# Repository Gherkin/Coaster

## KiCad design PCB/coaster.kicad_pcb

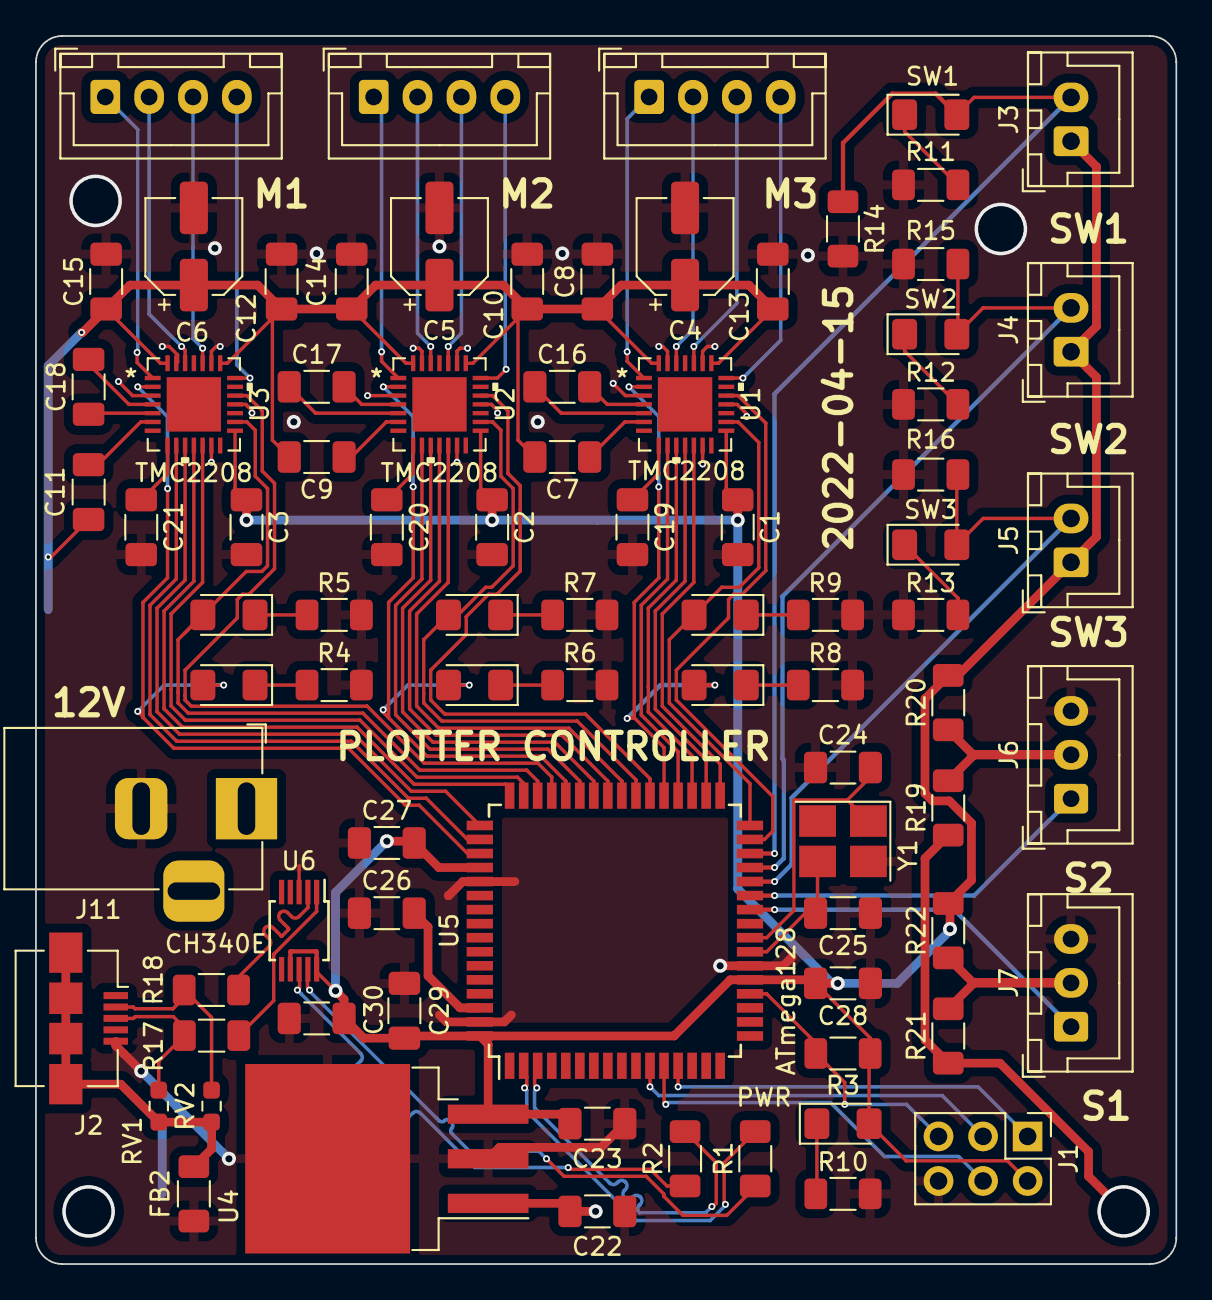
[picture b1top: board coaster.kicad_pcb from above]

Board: 2 copper layers, 65.0 x 70.0 mm, 83 parts (0 on the bottom side), 81 nets.

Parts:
C1, C2, C3, C7, C8, C9, C10, C11, C12, C13, C14, C15, C23, C26, C27, C28, C29, C30: 100n; C_1206_3216Metric_Pad1.33x1.80mm_HandSolder
C4, C5, C6: 100u; CP_Elec_5x5.4
C16, C17, C18: 22n; C_1206_3216Metric_Pad1.33x1.80mm_HandSolder
C19, C20, C21: 2.2u; C_1206_3216Metric_Pad1.33x1.80mm_HandSolder
C22: 0.33u; C_1206_3216Metric_Pad1.33x1.80mm_HandSolder
C24, C25: 20p; C_1206_3216Metric_Pad1.33x1.80mm_HandSolder
D1: M1EN; LED_1206_3216Metric_Pad1.42x1.75mm_HandSolder
D2: M1STEP; LED_1206_3216Metric_Pad1.42x1.75mm_HandSolder
D3: M2EN; LED_1206_3216Metric_Pad1.42x1.75mm_HandSolder
D4: M2STEP; LED_1206_3216Metric_Pad1.42x1.75mm_HandSolder
D5: M3EN; LED_1206_3216Metric_Pad1.42x1.75mm_HandSolder
D6: M3STEP; LED_1206_3216Metric_Pad1.42x1.75mm_HandSolder
D7: PWR; LED_1206_3216Metric_Pad1.42x1.75mm_HandSolder
D8: SW1; LED_1206_3216Metric_Pad1.42x1.75mm_HandSolder
D9: SW2; LED_1206_3216Metric_Pad1.42x1.75mm_HandSolder
D10: SW3; LED_1206_3216Metric_Pad1.42x1.75mm_HandSolder
FB2: FerriteBead; R_1206_3216Metric_Pad1.30x1.75mm_HandSolder
J1: AVR-ISP-6; PinHeader_2x03_P2.54mm_Vertical
J2: USB_B_Micro; USB_Micro-B_Amphenol_10104110_Horizontal
J3, J4, J5: Conn_01x02; JST_XH_B2B-XH-A_1x02_P2.50mm_Vertical
J6, J7: Conn_01x03; JST_XH_B3B-XH-A_1x03_P2.50mm_Vertical
J8, J9, J10: Conn_01x04; JST_XH_B4B-XH-A_1x04_P2.50mm_Vertical
J11: Barrel_Jack; BarrelJack_Horizontal
R1, R2: 1k; R_1206_3216Metric_Pad1.30x1.75mm_HandSolder
R3, R14, R15, R16: 10k; R_1206_3216Metric_Pad1.30x1.75mm_HandSolder
R4, R6, R8, R10: 100; R_1206_3216Metric_Pad1.30x1.75mm_HandSolder
R5, R7, R9, R11, R12, R13: 120; R_1206_3216Metric_Pad1.30x1.75mm_HandSolder
R17, R18: 22; R_1206_3216Metric_Pad1.30x1.75mm_HandSolder
R19, R20, R21, R22: 0; R_1206_3216Metric_Pad1.30x1.75mm_HandSolder
RV1, RV2: CG0603MLC-05E; R_0603_1608Metric_Pad0.98x0.95mm_HandSolder
U1, U2, U3: TMC2208; TMC2208-LA
U4: uA7805; TO-263-3_TabPin2
U5: ATmega128; TQFP-64_14x14mm_P0.8mm
U6: CH340E; MSOP-10_3x3mm_P0.5mm
Y1: 16MHz 12pF 60 Ohm +/- 10 ppm; Crystal_SMD_3225-4Pin_3.2x2.5mm_HandSoldering

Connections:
/5V: C1.1, C2.1, C3.1, C23.1, C27.2, C28.2, C29.1, C30.1, D7.2 (A), J1.2 (VCC), J3.1, J4.1, J5.1, R3.1, R20.2, R22.2, U1.15 (VCC_IO), U2.15 (VCC_IO), U3.15 (VCC_IO), U4.3 (OUT), U5.21 (VCC), U5.52 (VCC), U5.64 (AVCC), U6.7 (VCC), U6.10 (V3)
/9V: C4.1, C5.1, C6.1, C7.2, C8.1, C9.2, C10.1, C11.2, C12.1, C13.1, C14.1, C15.1, C22.1, J11.1, R19.1, R21.1, U1.22 (VS), U1.28 (VS), U2.22 (VS), U2.28 (VS), U3.22 (VS), U3.28 (VS), U4.1 (IN)
/AUART_N: R2.2, U5.3 (PE1)
/AUART_P: R1.2, U5.2 (PE0)
/M1AO1: J8.3, U3.24 (OA1)
/M1AO2: J8.4, U3.21 (OA2)
/M1BO1: J8.2, U3.26 (OB1)
/M1BO2: J8.1, U3.1 (OB2)
/M1CPI: C18.1, U3.5 (CPI)
/M1CPO: C18.2, U3.4 (CPO)
/M1DIAG: U3.11 (DIAG), U5.48 (PA3)
/M1DIR: U3.19 (DIR), U5.45 (PA6)
/M1EN: D1.2 (A), U3.2 (ENN), U5.51 (PA0)
/M1INDEX: U3.12 (INDEX), U5.47 (PA4)
/M1MS1: U3.9 (MS1), U5.50 (PA1)
/M1MS2: U3.10 (MS2), U5.49 (PA2)
/M1STEP: D2.2 (A), U3.16 (STEP), U5.46 (PA5)
/M2AO1: J9.3, U2.24 (OA1)
/M2AO2: J9.4, U2.21 (OA2)
/M2BO1: J9.2, U2.26 (OB1)
/M2BO2: J9.1, U2.1 (OB2)
/M2CPI: C17.1, U2.5 (CPI)
/M2CPO: C17.2, U2.4 (CPO)
/M2DIAG: U2.11 (DIAG), U5.41 (PC6)
/M2DIR: U2.19 (DIR), U5.38 (PC3)
/M2EN: D3.2 (A), U2.2 (ENN), U5.44 (PA7)
/M2INDEX: U2.12 (INDEX), U5.40 (PC5)
/M2MS1: U2.9 (MS1), U5.43 (PG2)
/M2MS2: U2.10 (MS2), U5.42 (PC7)
/M2STEP: D4.2 (A), U2.16 (STEP), U5.39 (PC4)
/M3AO1: J10.3, U1.24 (OA1)
/M3AO2: J10.4, U1.21 (OA2)
/M3BO1: J10.2, U1.26 (OB1)
/M3BO2: J10.1, U1.1 (OB2)
/M3CPI: C16.1, U1.5 (CPI)
/M3CPO: C16.2, U1.4 (CPO)
/M3DIAG: U1.11 (DIAG), U5.34 (PG1)
/M3DIR: U1.19 (DIR), U5.31 (PD6)
/M3EN: D5.2 (A), U1.2 (ENN), U5.37 (PC2)
/M3INDEX: U1.12 (INDEX), U5.33 (PG0)
/M3MS1: U1.9 (MS1), U5.36 (PC1)
/M3MS2: U1.10 (MS2), U5.35 (PC0)
/M3STEP: D6.2 (A), U1.16 (STEP), U5.32 (PD7)
/MISO: J1.1 (MISO), U5.13 (PB3)
/MOSI: J1.4 (MOSI), U5.12 (PB2)
/RESET: J1.5 (~RST), R3.2, U5.20 (~RESET)
/S1: J7.1, U5.26 (PD1)
/S2: J6.1, U5.27 (PD2)
/SCK: J1.3 (SCK), U5.11 (PB1)
/SW1: D8.2 (A), J3.2, R14.1, U5.30 (PD5)
/SW2: D9.2 (A), J4.2, R15.1, U5.29 (PD4)
/SW3: D10.2 (A), J5.2, R16.1, U5.28 (PD3)
/UART_N: R2.1, U6.8 (TXD)
/UART_P: R1.1, U6.9 (RXD)
/UD+: R17.2, U6.1 (UD+)
/UD-: R18.2, U6.2 (UD-)
/UUD+: J2.3 (D+), R17.1, RV1.1
/UUD-: J2.2 (D-), R18.1, RV2.1
/shield: FB2.1, J2.6 (Shield), RV1.2, RV2.2
GND: C1.2, C2.2, C3.2, C4.2, C5.2, C6.2, C8.2, C10.2, C12.2, C13.2, C14.2, C15.2, C19.2, C20.2, C21.2, C22.2, C23.2, C24.1, C25.1, C26.1, C27.1, C28.1, C29.2, C30.2, FB2.2, J1.6 (GND), J2.5 (GND), J6.3, J7.3, J11.2, R4.2, R5.2, R6.2, R7.2, R8.2, R9.2, R10.2, R11.1, R12.1, R13.1, R14.2, R15.2, R16.2, U1.3 (GND), U1.13 (CLK), U1.18 (GND), U1.23 (BRA), U1.27 (BRB), U2.3 (GND), U2.13 (CLK), U2.18 (GND), U2.23 (BRA), U2.27 (BRB), U3.3 (GND), U3.13 (CLK), U3.18 (GND), U3.23 (BRA), U3.27 (BRB), U4.2 (GND), U5.22 (GND), U5.53 (GND), U5.63 (GND), U6.3 (GND), Y1.2 (GND), Y1.4 (GND)
unnamed: C7.1, U1.6 (VCP)
unnamed: C9.1, U2.6 (VCP)
unnamed: C11.1, U3.6 (VCP)
unnamed: C19.1, U1.8 (5VOUT)
unnamed: C20.1, U2.8 (5VOUT)
unnamed: C21.1, U3.8 (5VOUT)
unnamed: C24.2, U5.24 (XTAL1), Y1.1 (IN/OUT)
unnamed: C25.2, U5.23 (XTAL2), Y1.3 (OUT/IN)
unnamed: C26.2, U5.62 (AREF)
unnamed: D1.1 (K), R4.1
unnamed: D2.1 (K), R5.1
unnamed: D3.1 (K), R6.1
unnamed: D4.1 (K), R7.1
unnamed: D5.1 (K), R8.1
unnamed: D6.1 (K), R9.1
unnamed: D7.1 (K), R10.1
unnamed: D8.1 (K), R11.2
unnamed: D9.1 (K), R12.2
unnamed: D10.1 (K), R13.2
unnamed: J6.2, R19.2, R20.1
unnamed: J7.2, R21.2, R22.1

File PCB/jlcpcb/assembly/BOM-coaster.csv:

Comment,Designator,Footprint,LCSC
22n,"C16,C17,C18",C_1206_3216Metric_Pad1.33x1.80mm_HandSolder,C113907
TMC2208,"U1,U2,U3",TMC2208-LA,C115944
FerriteBead,FB2,R_1206_3216Metric_Pad1.30x1.75mm_HandSolder,C139169
20p,"C24,C25",C_1206_3216Metric_Pad1.33x1.80mm_HandSolder,C162447
0,"R19,R20,R21,R22",R_1206_3216Metric_Pad1.30x1.75mm_HandSolder,C17888
100,"R10,R4,R6,R8",R_1206_3216Metric_Pad1.30x1.75mm_HandSolder,C17901
10k,"R14,R15,R16,R3",R_1206_3216Metric_Pad1.30x1.75mm_HandSolder,C17902
120,"R11,R12,R13,R5,R7,R9",R_1206_3216Metric_Pad1.30x1.75mm_HandSolder,C17909
ATmega128,U5,TQFP-64_14x14mm_P0.8mm,C183188
CG0603MLC-05E,"RV1,RV2",R_0603_1608Metric_Pad0.98x0.95mm_HandSolder,C20960
100n,"C1,C10,C11,C12,C13,C14,C15,C2,C23,C26,C27,C28,C29,C3,C30,C7,C8,C9",C_1206_3216Metric_Pad1.33x1.80mm_HandSolder,C24497
0.33u,C22,C_1206_3216Metric_Pad1.33x1.80mm_HandSolder,C307572
1k,"R1,R2",R_1206_3216Metric_Pad1.30x1.75mm_HandSolder,C4410
100u,"C4,C5,C6",CP_Elec_5x5.4,C487302
2.2u,"C19,C20,C21",C_1206_3216Metric_Pad1.33x1.80mm_HandSolder,C50254
22,"R17,R18",R_1206_3216Metric_Pad1.30x1.75mm_HandSolder,C5672
M1EN,"D1,D3,D5,D7",LED_1206_3216Metric_Pad1.42x1.75mm_HandSolder,C84273
16MHz 12pF 60 Ohm +/- 10 ppm,Y1,Crystal_SMD_3225-4Pin_3.2x2.5mm_HandSoldering,C89371
SW3,"D10,D2,D4,D6,D8,D9",LED_1206_3216Metric_Pad1.42x1.75mm_HandSolder,C93133
uA7805,U4,TO-263-3_TabPin2,C962135
CH340E,U6,MSOP-10_3x3mm_P0.5mm,C99652
Conn_01x04,J8,JST_XH_B4B-XH-A_1x04_P2.50mm_Vertical,
Barrel_Jack,J11,BarrelJack_Horizontal,
AVR-ISP-6,J1,PinHeader_2x03_P2.54mm_Vertical,
Conn_01x04,J9,JST_XH_B4B-XH-A_1x04_P2.50mm_Vertical,
Conn_01x02,J3,JST_XH_B2B-XH-A_1x02_P2.50mm_Vertical,
Conn_01x02,J5,JST_XH_B2B-XH-A_1x02_P2.50mm_Vertical,
Conn_01x02,J4,JST_XH_B2B-XH-A_1x02_P2.50mm_Vertical,
Conn_01x03,J7,JST_XH_B3B-XH-A_1x03_P2.50mm_Vertical,
USB_B_Micro,J2,USB_Micro-B_Amphenol_10104110_Horizontal,
Conn_01x04,J10,JST_XH_B4B-XH-A_1x04_P2.50mm_Vertical,
Conn_01x03,J6,JST_XH_B3B-XH-A_1x03_P2.50mm_Vertical,

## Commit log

2021-12-11 init
2022-04-19 init!
2022-04-19 moved pcb files to pcb dir
2022-04-19 added the fusion file
2022-04-19 cleaned in pcb
2022-04-20 added some sourcing

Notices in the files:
parts and their libraries:
Copyright 2021 Accelerated Designs. All rights reserved.
